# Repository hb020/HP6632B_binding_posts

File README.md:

HP 66332A and HP 6632B-6634B Frontpanel Binding Post PCB
===================
This repository contains the schematics for a PCB to mount frontpanel binding post on an HP 6632B (and siblings) power supply. It is an adaption of the original A4 PCB used in option #020 units.

In contrast to the original option #20 PCB, this board breaks out the sense connections as well and also the chassis ground. This makes connecting multiple HP 663xB in parallel possible. On the downside, this requires connecting the sense pins externally.   

The components chosen allow the board to be used on all variants of the HP 663xB family - even the 100 V 6634B. A variety of different binding posts can be used. There are HP/Agilent versions available on Ebay. Examples:
- Pomona 4243-0 ([Digikey](https://www.digikey.de/en/products/detail/pomona-electronics/4243-0/604321)) and 3760-5 ([Digikey](https://www.digikey.de/en/products/detail/pomona-electronics/3760-5/736554)).
- EZ-Hook 9406 ([Digikey](https://www.digikey.fr/en/products/detail/e-z-hook/9406/574036)) (only to be found in red and black as a set or individually under the name EZ-Hook 9280BLK or 9280RED)

The final result looks like this:

The following changes were made to Patrick Baus's original version:

- the terminals are moved around to match a more standard layout.
- added documentation about the connectivity to the main board.
- the wire connections are moved to better align with the hole in the chassis behind the posts.
- the slot in the PCB for the front panel fixation screw is widened a bit to allow more freedom.
- newer KiCad version (6.0).
- added a FreeCAD model.
- uses a 3D printed [Front Terminal Adapter](freecad/Front_Terminal_Adapter.stl) (also see below) for more rigidity.

About
-----
The root folder contains the KiCAD files.

The gerber files can be found in the [/gerber](gerber/) folder.

A 3D model from FreeCAD can be found in the [/freecad](freecad/) folder. That model was used to determine the placement of the connector and the ground wire.

Labels for a Dymo printer can be found in the [/labels](labels/) folder.

Test scripts (via Prologix USB-GPIB) can be found in the [/testscripts](testscripts/) folder.

Related Repositories and info
-----------------------------

See the following repositories for more information

KiCAD schematic libraries: https://github.com/PatrickBaus/KiCad-libraries

A "HP 66xxA 65xxA PSU Front Panel Binding Post Adapter" plate from [NearFarMedia](https://www.thingiverse.com/thing:4299873) is recommended. It is also [included in the FreeCad file](freecad/Front_Terminal_Adapter.stl). The slots for the binding posts might be a bit tighter, but it works superbly.

I'd also recommend to look at [Barbouri's efforts](https://www.barbouri.com/2021/04/23/hewlett-packard-agilent-6632b-upgrade/) for his upgrade.

You may want to combine this with the [option 760 relay board](https://github.com/hb020/HP6632B_relay_board).

License
-------

This work is released under the Cern OHL v.1.2
See www.ohwr.org/licenses/cern-ohl/v1.2 or the included LICENSE file for more information.

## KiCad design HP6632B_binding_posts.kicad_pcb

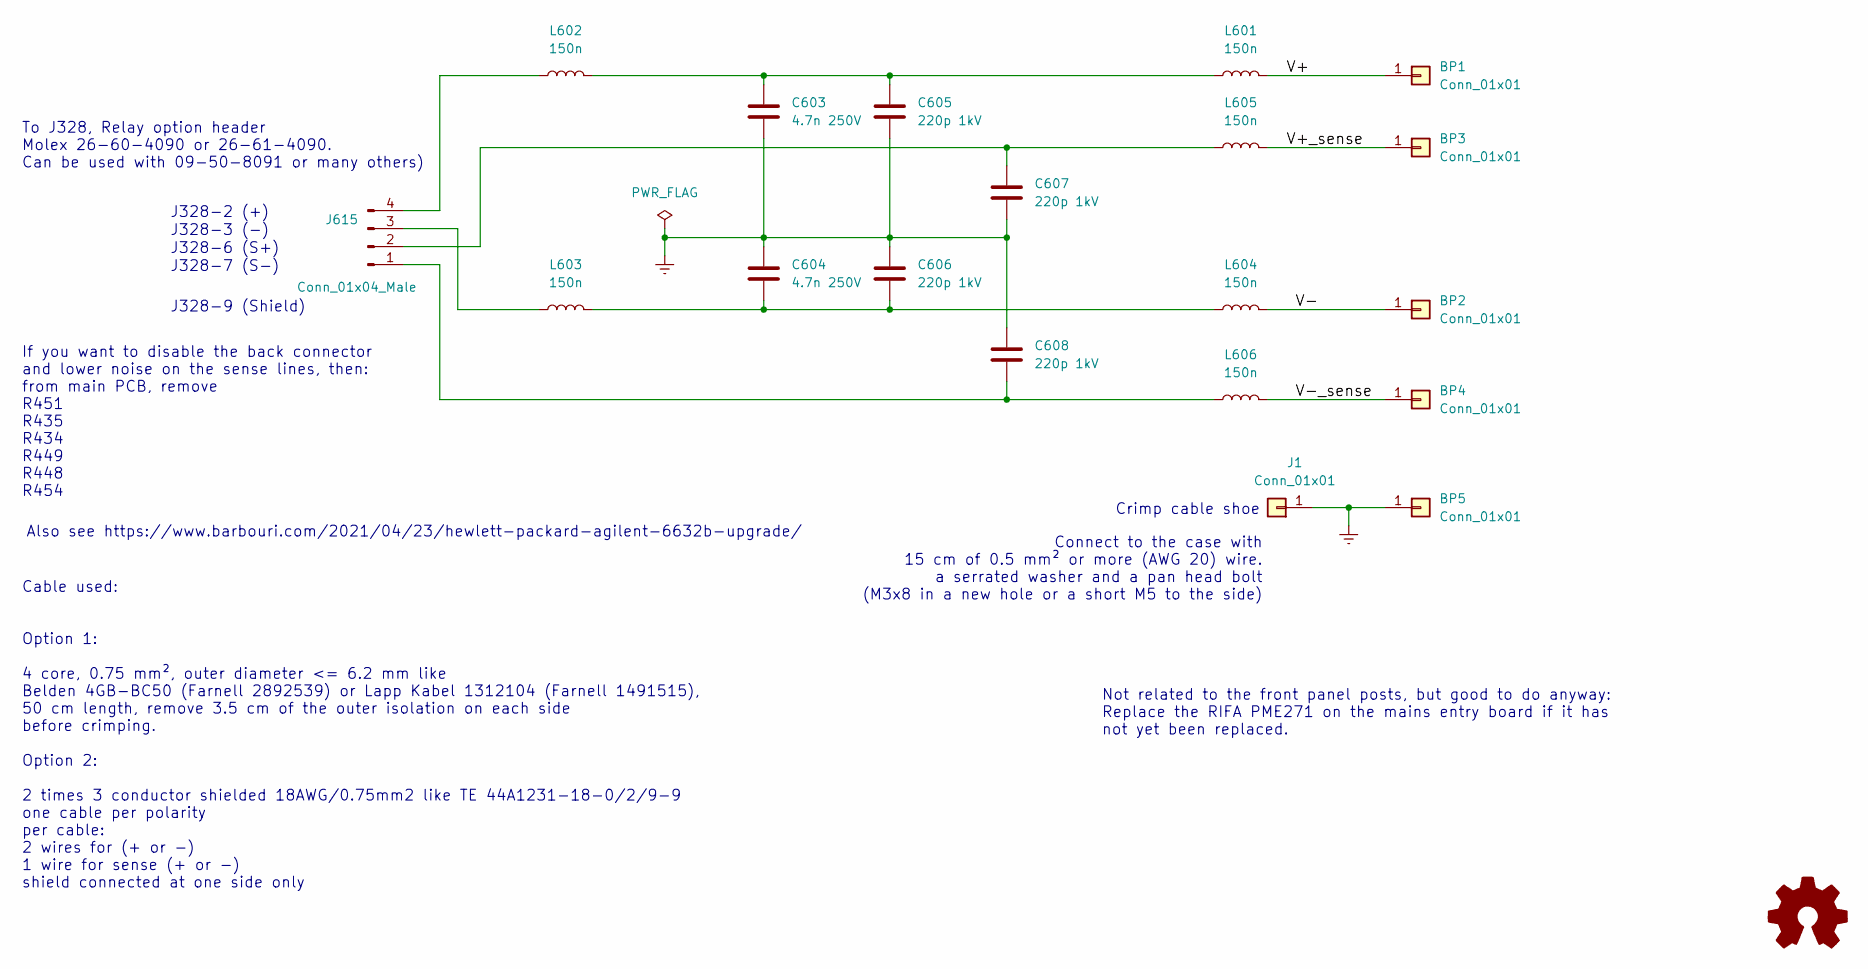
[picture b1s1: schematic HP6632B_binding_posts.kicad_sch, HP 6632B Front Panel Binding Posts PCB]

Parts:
BP1, BP2, BP3, BP4, BP5: Conn_01x01; MountingHole_3.5mm_Pad
C603, C604: 4.7n 250V; C_Rect_L13.0mm_W5.0mm_P10.00mm_FKS3_FKP3_MKS4
C605, C606, C607, C608: 220p 1kV; C_Disc_D7.5mm_W4.4mm_P5.00mm
J1: Conn_01x01; TestPoint_THTPad_D4.0mm_Drill2.0mm
J615: Conn_01x04_Male; Molex_KK-396_A-41791-0004_1x04_P3.96mm_Vertical
L601, L602, L603, L604, L605, L606: 150n; L_1008_2520Metric_Pad1.43x2.20mm_HandSolder
LOGO1: Logo_Open_Hardware_Small; OSHW-Logo_7.5x8mm_SilkScreen

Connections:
/V+: BP1.1, L601.2
/V+_sense: BP3.1, L605.2
/V-: BP2.1, L604.2
/V-_sense: BP4.1, L606.2
Earth: BP5.1, C603.2, C604.1, C605.2, C606.1, C607.2, C608.1, J1.1
unnamed: C603.1, C605.1, L601.1, L602.2
unnamed: C604.2, C606.2, L603.2, L604.1
unnamed: C608.2, J615.1, L606.1
unnamed: C607.1, J615.2, L605.1
unnamed: J615.3, L603.1
unnamed: J615.4, L602.1

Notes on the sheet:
J328-6 (S+)
J328-2 (+)
Connect to the case with 15 cm of 0.5 mm² or more (AWG 20) wire. a serrated washer and a pan head bolt (M3x8 in a new hole or a short M5 to the side)
J328-3 (-)
J328-7 (S-)
To J328, Relay option header Molex 26-60-4090 or 26-61-4090. Can be used with 09-50-8091 or many others)
Cable used: Option 1: 4 core, 0.75 mm², outer diameter <= 6.2 mm like Belden 4GB-BC50 (Farnell 2892539) or Lapp Kabel 1312104 (Farnell 1491515), 50 cm length, remove 3.5 cm of the outer isolation on each side before crimping. Option 2: 2 times 3 conductor shielded 18AWG/0.75mm2 like TE 44A1231-18-0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
Crimp cable shoe
Also see https://www.barbouri.com/2021/04/23/hewlett-packard-agilent-6632b-upgrade/
Not related to the front panel posts, but good to do anyway: Replace the RIFA PME271 on the mains entry board if it has not yet been replaced.
J328-9 (Shield)
If you want to disable the back connector and lower noise on the sense lines, then: from main PCB, remove R451 R435 R434 R449 R448 R454

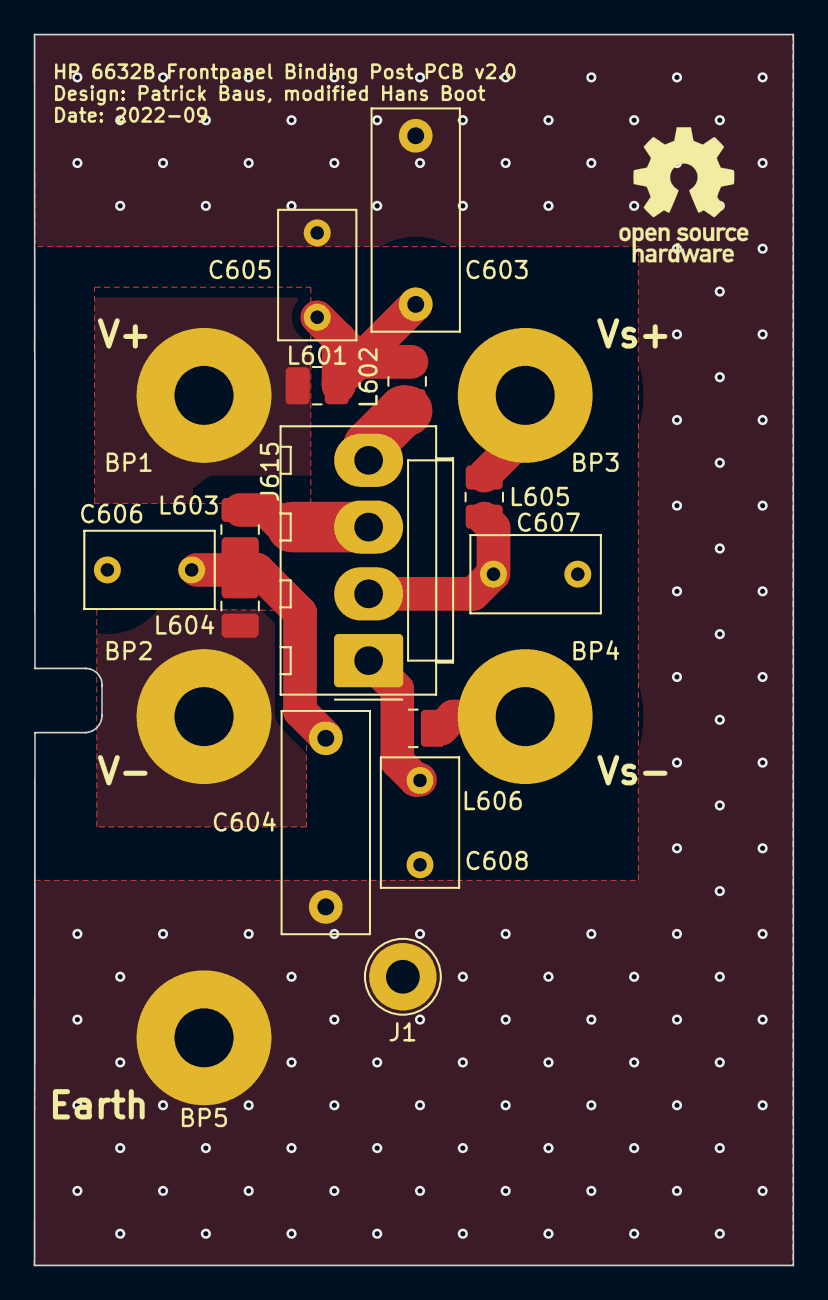
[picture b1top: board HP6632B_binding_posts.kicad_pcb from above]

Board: 2 copper layers, 45.0 x 73.0 mm, 20 parts (0 on the bottom side), 11 nets.

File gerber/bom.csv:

Designator,Footprint,Quantity,Value,LCSC Part #
"BP1, BP2, BP3, BP4, BP5",MountingHole_3.5mm_Pad,5,Conn_01x01,
"C603, C604",C_Rect_L13.0mm_W5.0mm_P10.00mm_FKS3_FKP3_MKS4,2,4.7n,
"C605, C606, C607, C608",C_Disc_D7.5mm_W4.4mm_P5.00mm,4,220p,
J1,TestPoint_THTPad_D4.0mm_Drill2.0mm,1,Conn_01x01,
J615,Molex_KK-396_A-41791-0004_1x04_P3.96mm_Vertical,1,Conn_01x04_Male,
"L601, L602, L603, L604, L605, L606",L_1008_2520Metric_Pad1.43x2.20mm_HandSolder,6,150n,
LOGO1,OSHW-Logo_7.5x8mm_SilkScreen,1,Logo_Open_Hardware_Small,

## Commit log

2020-10-23 Updated to v1.1 Moved cutout 1.5 mm down Decreased size of earth connection J1
2020-10-23 Added readme Added binding posts to the BOM
2020-10-23 Update README.md
    Fixed typo in link
2020-10-23 Added BOM and costs file
2020-10-23 Added missing crimp connector
2020-10-23 Update README.md
    Fixed typo
2021-07-02 Increased GND plane clearance to 0.25 mm
2022-10-01 my updates
2022-10-01 oops
2022-10-01 cleaning up
2022-10-01 tweak image
2022-10-16 clarifications
2023-08-08 added 3d models of plate
2023-08-08 update to newer kicad version, added interactive BOM
2023-08-08 removed superfluous files
2023-08-09 better doc
2023-08-21 more doc
2023-09-01 a bit more freedom in testing
2024-03-24 remove some glitches in the test script

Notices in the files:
HP6632B_binding_posts.kicad_pcb:
Copyright (©) 2020, Patrick Baus
Licensed under CERN OHL v.1.2
